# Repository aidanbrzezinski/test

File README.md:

<h1 align="center">Board Name</h1>

<p align="center" width="100%">
  
</p>

<p align="center">
  
&nbsp; &nbsp; &nbsp; &nbsp;
  
</p>

***

<p align="center">
  
&nbsp; &nbsp; &nbsp; &nbsp;
  
</p>

***

## SPECIFICATIONS

| Parameter | Value |
| --- | --- |
| Dimensions | 100.0 × 50.0 mm |

***

## DIRECTORY STRUCTURE

    .
    ├─ 3D                 # STEP 3D model export
    ├─ Images             # Pictures and renders
    │
    ├─ kibot_resources    # External resources for KiBot
    │  ├─ colors          # Color theme for KiCad
    │  ├─ fonts           # Fonts used in the project
    │  ├─ scripts         # External scripts used with KiBot
    │  └─ templates       # Templates for KiBot generated reports
    │
    ├─ kibot_yaml         # KiBot YAML config files
    ├─ Logos              # Logos
    ├─ Reports            # Reports for ERC/DRC
    ├─ Templates          # Title block templates
    │
    └─ Variants           # Outputs for custom (non-standard) variants

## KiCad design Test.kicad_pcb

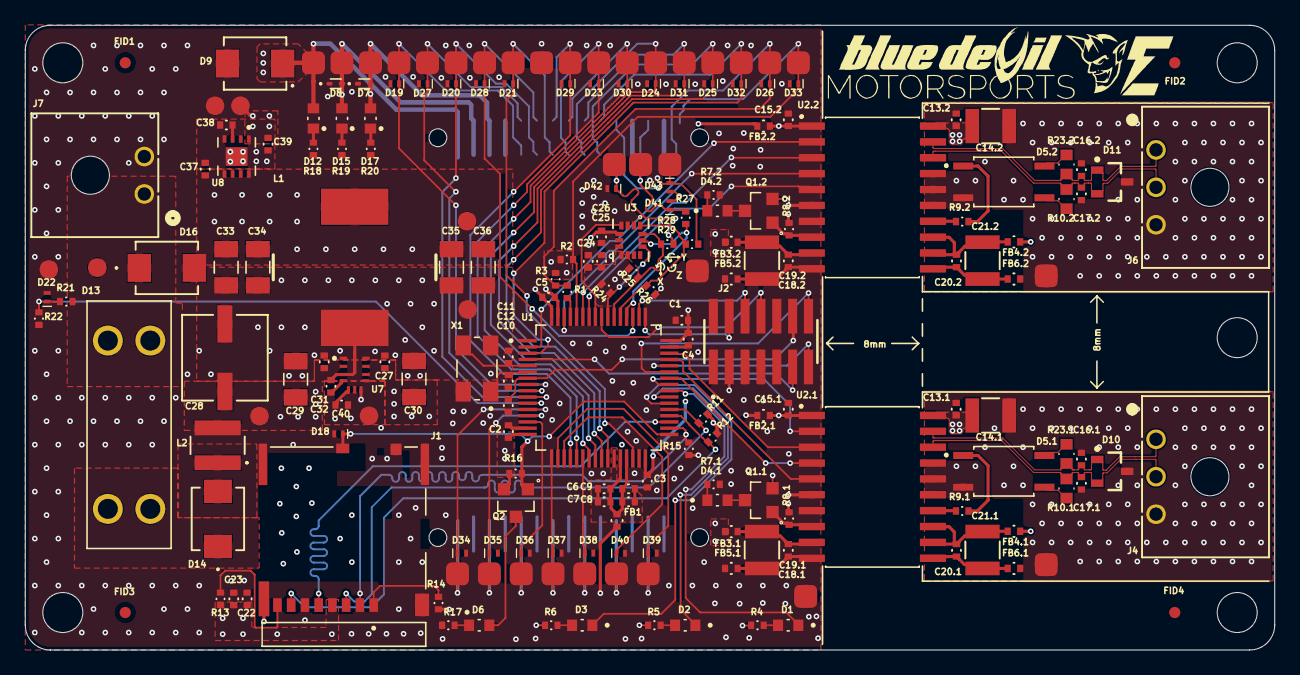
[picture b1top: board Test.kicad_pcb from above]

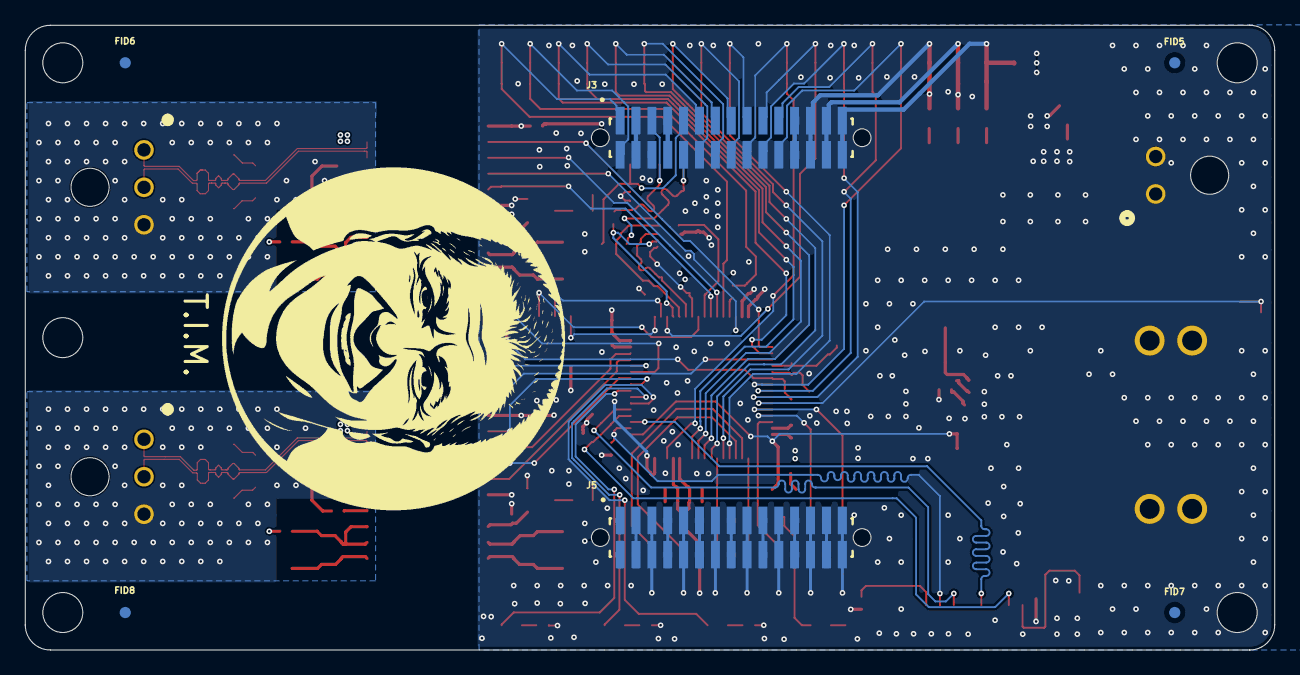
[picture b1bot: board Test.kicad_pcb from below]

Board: 4 copper layers, 100.0 x 50.0 mm, 206 parts (6 on the bottom side), 111 nets.

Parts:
C1: 4.7uF; CL05
C2, C3, C4, C5, C6, C10, C13.1, C13.2, C15.1, C15.2, C23, C25, C26, C32: 100nF; CL05
C7, C8, C37, C40: 1uF; CL05
C9, C19.1, C19.2, C20.1, C20.2, C38: 10nF; CL05
C11, C12: 12pF; CL05
C14.1, C14.2, C18.1, C18.2, C21.1, C21.2: 47uF; CAP_CL32_SAM
C16.1, C16.2, C17.1, C17.2: 68pF; CL05
C22, C24, C39: 10uF; CL05
C27, C31: 0.1uF; CL05
C28: 47uF; CAP_UCD_6P3X7P7_NCH
C29, C30: 4.7uF; CAPC3216X190N
C33, C34, C35, C36: 22uF; CAPC3216X190N
D1, D2, D3: LTST-C190TBKT; LEDC1608X35N
D4.1, D4.2: LTST-C190KRKT; LEDC1608X35N
D5.1, D5.2: TLP172AM(TPR,E; SOIC254P700X220-4N
D6, D12, D15, D17: LTST-C190KGKT; LEDC1608X35N
D7: ESD9B3.3ST5G; SODFL1006X40N
D8: ESD9B5.0ST5G; SODFL1006X40N
D9, D14: CDBA340L-HF; DO-214AASMB_J-BEND_LTF
D10, D11: PESD2CANFD24LT-QR; SOT95P245X110-3N
D13: 3557-2; FUSE_3557-2
D16: SMBJ15A; DO-214AASMB_J-BEND_LTF
D18, D19, D20, D21, D22, D23, D24, D25, D26, D27, D28, D29, D30, D31, D32, D33, D34, D35, D36, D37, D38, D39, D40, D41, D42, D43: TPD1E04U04DPYR; DPY2_TEX
FB1, FB2.1, FB2.2, FB3.1, FB3.2, FB4.1, FB4.2, FB5.1, FB5.2, FB6.1, FB6.2: 330 Ohms @ 100 MHz; BLM15EX331SN1D
FID1, FID2, FID3, FID4, FID5, FID6, FID7, FID8: DNP; FID90X190
J1: 503398-1892; MOLEX_503398-1892
J2: FTSH-107-01-L-DV-K-TR; SAMTEC_FTSH-107-01-X-DV-K-TR
J3, J5: SFM-115-02-L-D-A-K-TR; SAMTEC_SFM-115-02-X-D-A
J4, J6: 0436500300; CONN_SD-43650-001_03_MOL
J7: 0436500200; CONN_SD-43650-001_02_MOL
L1: 10 µH; PM124SH-100M-RC
L2: 2.2uH; IND_TAIYO_NRS4018_TAY
Q1.1, Q1.2, Q2: BSS84; SOT95P240X120-3N
R1, R27, R28, R29: 0; RMCF0402FT
R2, R3, R18: 2k; RMCF0402FT
R4, R5, R6, R9.1, R9.2, R17, R20: 240; RMCF0402FT
R7.1, R7.2, R19: 560R; RMCF0402FT
R8.1, R8.2: 5.1k; RMCF0402FT
R10.1, R10.2, R23.1, R23.2: 59R; RESC1508X50N
R11, R12, R13, R14, R15, R16, R24, R25, R26: 10K; RMCF0402FT
R21: 120K; RMCF0402FT
R22: 10k; RMCF0402FT
TP1, TP2, TP3, TP4, TP5, TP6, TP7, TP38: NA; TP150-NO3D
TP8, TP9, TP10, TP11, TP12, TP13, TP14, TP15, TP16, TP17, TP18, TP19, TP20, TP21, TP22, TP23, TP24, TP25, TP26, TP27, TP28, TP29, TP30, TP31, TP32, TP33, TP34, TP35, TP36, TP37, TP39, TP40: TP-Square; TPS180
U1: STM32G474RCT6; QFP50P1200X1200X160-64N
U2.1, U2.2: ISOW1044DFMR; XCVR_ISOW1044BDFMR
U3: ASM330LHHG1TR; LGA14_2P5X3_STM
U7: LMR33620AQ5RNXTQ1; RNX0012B
U8: TPS73733QDRBRQ1; IC_DRV8601DRBT
X1: 8Mhz; XTAL_ECS-80-10-30B-CWN-TR

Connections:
3V3: C1.2, C2.2, C3.2, C4.2, C5.2, C22.1, C23.1, C24.2, C25.1, C26.1, C39.2, D7.2, D17.1, FB1.1, FB2.1.1, FB2.2.1, J1.4, J2.03, J3.05, J3.06, Q2.2, R2.1, R3.1, R4.1, R5.1, R6.1, R11.1, R12.1, R13.1, R14.1, R15.1, R16.1, R24.1, R25.1, R26.1, TP3.1, TP10.1, U1.16, U1.32, U1.48, U1.64, U3.5, U3.8, U8.1
3V3_FILT: C6.2, C7.2, C8.2, C9.2, FB1.2, U1.28, U1.29
5V: C33.2, C34.2, C35.2, C36.2, C37.2, D8.2, D15.1, FB3.1.1, FB3.2.1, J3.03, J3.04, L1.2, Q1.1.2, Q1.2.2, TP2.1, TP11.1, U7.7, U8.5, U8.8
12V: C27.2, C28.2, C29.2, C30.2, C31.2, D9.1, D12.1, J3.01, J3.02, L2.2, TP1.1, TP12.1, U7.2, U7.9, U7.10
ADC1_IN1: D34.1, J5.01, J5.02, TP28.1, U1.12
ADC1_IN2: D35.1, J5.05, J5.06, TP29.1, U1.13
ADC1_IN3: D36.1, J5.09, J5.10, TP30.1, U1.14
ADC1_IN4: D37.1, J5.13, J5.14, TP31.1, U1.17
ADC2_IN5: D38.1, J5.17, J5.18, TP32.1, U1.22
CANFD1TERM.1_N: D5.1.4, R23.1.2
CANFD1TERM.1_P: D5.1.6, R10.1.1
CANFD1TERM.2_N: D5.2.4, R23.2.2
CANFD1TERM.2_P: D5.2.6, R10.2.1
CANFD.1_N: C17.1.2, D10.2, J4.2, R23.1.1, U2.1.18
CANFD.1_P: C16.1.1, D10.1, J4.1, R10.1.2, U2.1.19
CANFD.2_N: C17.2.2, D11.2, J6.2, R23.2.1, U2.2.18
CANFD.2_P: C16.2.1, D11.1, J6.1, R10.2.2, U2.2.19
CAN_TERM_1: U1.41, U2.1.2
CAN_TERM_2: U1.2, U2.2.2
DAC1_OUT1: D39.1, J5.25, J5.26, TP33.1, U1.18
DAC1_OUT2: D40.1, J5.21, J5.22, TP34.1, U1.19
FDCAN1_RX: U1.45, U2.1.5
FDCAN1_STB: U1.42, U2.1.4
FDCAN1_TX: U1.46, U2.1.3
FDCAN2_RX: U1.58, U2.2.5
FDCAN2_STB: U1.62, U2.2.4
FDCAN2_TX: U1.59, U2.2.3
GND: C1.1, C2.1, C3.1, C4.1, C5.1, C10.1, C11.1, C12.1, C15.1.1, C15.2.1, C22.2, C23.2, C24.1, C25.2, C26.2, C27.1, C28.1, C29.1, C30.1, C31.1, C33.1, C34.1, C35.1, C36.1, C37.1, C38.1, C39.1, C40.1, D7.1, D8.1, D9.2, D16.2, D18.2, D19.2, D20.2, D21.2, D22.2, D23.2, D24.2, D25.2, D26.2, D27.2, D28.2, D29.2, D30.2, D31.2, D32.2, D33.2, D34.2, D35.2, D36.2, D37.2, D38.2, D39.2, D40.2, D41.2, D42.2, D43.2, FB5.1.1, FB5.2.1, J1.6, J1.9, J1.P1, J1.P2, J1.P3, J1.P4, J2.05, J2.07, J3.07, J3.08, J3.23, J3.24, J3.25, J3.27, J3.28, J5.03, J5.04, J5.07, J5.08, J5.11, J5.12, J5.15, J5.16, J5.19, J5.20, J5.23, J5.24, J5.27, J5.28, J5.29, J5.30, J7.2, R7.1.1, R7.2.1, R17.2, R18.2, R19.2, R20.2, R22.1, TP4.1, TP5.1, TP6.1, TP9.1, TP16.1, TP36.1, TP38.1, U1.15, U1.31, U1.47, U1.63, U2.1.6, U2.2.6, U3.2, U3.3, U3.6, U3.7, U7.1, U7.6, U7.11, U8.4, U8.9, X1.2, X1.4
GNDDETECT: J2.11, U1.4
GPIO_1: D29.1, J3.14, TP23.1, U1.20
GPIO_2: D23.1, J3.15, TP17.1, U1.21
GPIO_3: D30.1, J3.16, TP24.1, U1.23
GPIO_4: D24.1, J3.17, TP18.1, U1.24
GPIO_5: D31.1, J3.18, TP25.1, U1.25
GPIO_6: D25.1, J3.19, TP19.1, U1.26
GPIO_7: D32.1, J3.20, TP26.1, U1.3
GPIO_CAN1LED: D2.2, U1.39
GPIO_CAN2LED: D3.2, U1.38
GPIO_HBLED: D1.2, U1.40
I2C1_SCL: D26.1, J3.29, R1.2, R3.2, TP20.1
I2C1_SDA: D33.1, J3.30, R2.2, TP27.1, U1.60
IMU_CS: R24.2, U1.55, U3.12
IMU_INT: U1.57, U3.4
IMU_MISO: R26.2, R29.1, U1.53, U3.1
IMU_MOSI: R25.2, R28.1, U1.54, U3.14
IMU_SCK: R27.1, U1.52, U3.13
ISO_5V.1: C13.1.2, C14.1.2, FB4.1.2, U2.1.20
ISO_5V.2: C13.2.2, C14.2.2, FB4.2.2, U2.2.20
ISO_GND.1: C13.1.1, C14.1.1, C16.1.2, C17.1.1, D5.1.3, D10.3, FB6.1.2, J4.3, TP35.1, U2.1.15, U2.1.16, U2.1.17
ISO_GND.2: C13.2.1, C14.2.1, C16.2.2, C17.2.1, D5.2.3, D11.3, FB6.2.2, J6.3, TP37.1, U2.2.15, U2.2.16, U2.2.17
NRST: C10.2, J2.12, U1.7
NetC15.1_2: C15.1.2, FB2.1.2, R8.1.1, U2.1.1
NetC15.2_2: C15.2.2, FB2.2.2, R8.2.1, U2.2.1
NetC18.1_1: C18.1.1, C19.1.1, FB5.1.2, U2.1.10
NetC18.1_2: C18.1.2, C19.1.2, FB3.1.2, U2.1.9
NetC18.2_1: C18.2.1, C19.2.1, FB5.2.2, U2.2.10
NetC18.2_2: C18.2.2, C19.2.2, FB3.2.2, U2.2.9
NetC20.1_1: C20.1.1, C21.1.1, FB6.1.1, U2.1.11
NetC20.1_2: C20.1.2, C21.1.2, FB4.1.1, U2.1.12, U2.1.13
NetC20.2_1: C20.2.1, C21.2.1, FB6.2.1, U2.2.11
NetC20.2_2: C20.2.2, C21.2.2, FB4.2.1, U2.2.12, U2.2.13
NetC32_1: C32.1, U7.4
NetC32_2: C32.2, L1.1, U7.3, U7.12
NetC38_2: C38.2, U8.3
NetC40_2: C40.2, U7.5
NetD1_1: D1.1, R4.2
NetD2_1: D2.1, R5.2
NetD3_1: D3.1, R6.2
NetD4.1_1: D4.1.1, Q1.1.3
NetD4.1_2: D4.1.2, R7.1.2
NetD4.2_1: D4.2.1, Q1.2.3
NetD4.2_2: D4.2.2, R7.2.2
NetD5.1_1: D5.1.1, R9.1.2
NetD5.2_1: D5.2.1, R9.2.2
NetD6_1: D6.1, Q2.3
NetD6_2: D6.2, R17.1
NetD12_2: D12.2, R18.1
NetD13_2_1: D13.2_1, D13.2_2, D14.1
NetD14_2: D14.2, L2.1
NetD15_2: D15.2, R19.1
NetD17_2: D17.2, R20.1
NetJ1_1: J1.1, R14.2
NetJ1_8: J1.8, R13.2
NetQ1.1_1: Q1.1.1, R8.1.2, U2.1.8
NetQ1.2_1: Q1.2.1, R8.2.2, U2.2.8
NetR1_1: R1.1, U1.61
SD_CS: J1.2, R15.2, U1.34
SD_Detect: D18.1, J1.10, Q2.1, R16.2, U1.33
SD_MISO: J1.7, R12.2, U1.36
SD_MOSI: J1.3, R11.2, U1.37
SD_SCK: J1.5, U1.35
SPI_MISO: D43.1, J3.22, R29.2, TP40.1
SPI_MOSI: D42.1, J3.21, R28.2, TP39.1
SPI_SCK: D41.1, J3.26, R27.2, TP8.1
SWCLK: J2.06, U1.50
SWDIO: J2.04, U1.49
SWO: J2.08, U1.56
TERM_TOGGLE.1: R9.1.1, U2.1.14
TERM_TOGGLE.2: R9.2.1, U2.2.14
TIM1_CH1: D19.1, J3.09, TP13.1, U1.8
TIM1_CH2: D27.1, J3.10, TP21.1, U1.9
TIM1_CH3: D20.1, J3.11, TP14.1, U1.10
TIM2_CH1: D28.1, J3.12, TP22.1, U1.51
TIM2_CH3: D21.1, J3.13, TP15.1, U1.30
T_VCP_RX: J2.13, U1.44
T_VCP_TX: J2.14, U1.43
VBAT: D13.1_1, D13.1_2, D16.1, J7.1, R21.2, TP7.1
VBAT_ADC: D22.1, R21.1, R22.2, U1.11
VSSA: C6.1, C7.1, C8.1, C9.1, U1.27
XIN: C11.2, U1.5, X1.3
XOUT: C12.2, U1.6, X1.1
